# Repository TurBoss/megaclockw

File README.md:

# MegaClockW

Remote control your MD mods over wifi

MegaClockW Allows to control Region/Lang, video mode HZ, reset console and control the cpu mhz from 5.0 to 12.8

## Software Installation

Download Thonny or rshell

Upload the MicroPython uf2 on the Raspberry pi pico W
by booting in program mode by holding the push button and connect the USB cable

Upload the project files found in the src directory to the root of the pico using Thonny or rshell

https://github.com/dhylands/rshell

https://github.com/thonny/thonny/releases

https://micropython.org/download/rp2-pico-w/

## Hardware Installation

## Development

* [GitHub Repo](https://github.com/TurBoss/megaclockw/)
* [Issue Tracker](https://github.com/TurBoss/megaclockw/issues)

## Documentation and Help

* [Discord](https://discord.gg/8Ck5gNkA)

## DISCLAIMER

THE AUTHORS OF THIS SOFTWARE ACCEPT ABSOLUTELY NO LIABILITY FOR
ANY HARM OR LOSS RESULTING FROM ITS USE.  IT IS _EXTREMELY_ UNWISE
TO RELY ON SOFTWARE ALONE FOR SAFETY.  Any machinery capable of
harming persons must have provisions for completely removing power
from all motors, etc, before persons enter any danger area.  All
machinery must be designed to comply with local and national safety
codes, and the authors of this software can not, and do not, take
any responsibility for such compliance.

This software is released under the GPLv3.

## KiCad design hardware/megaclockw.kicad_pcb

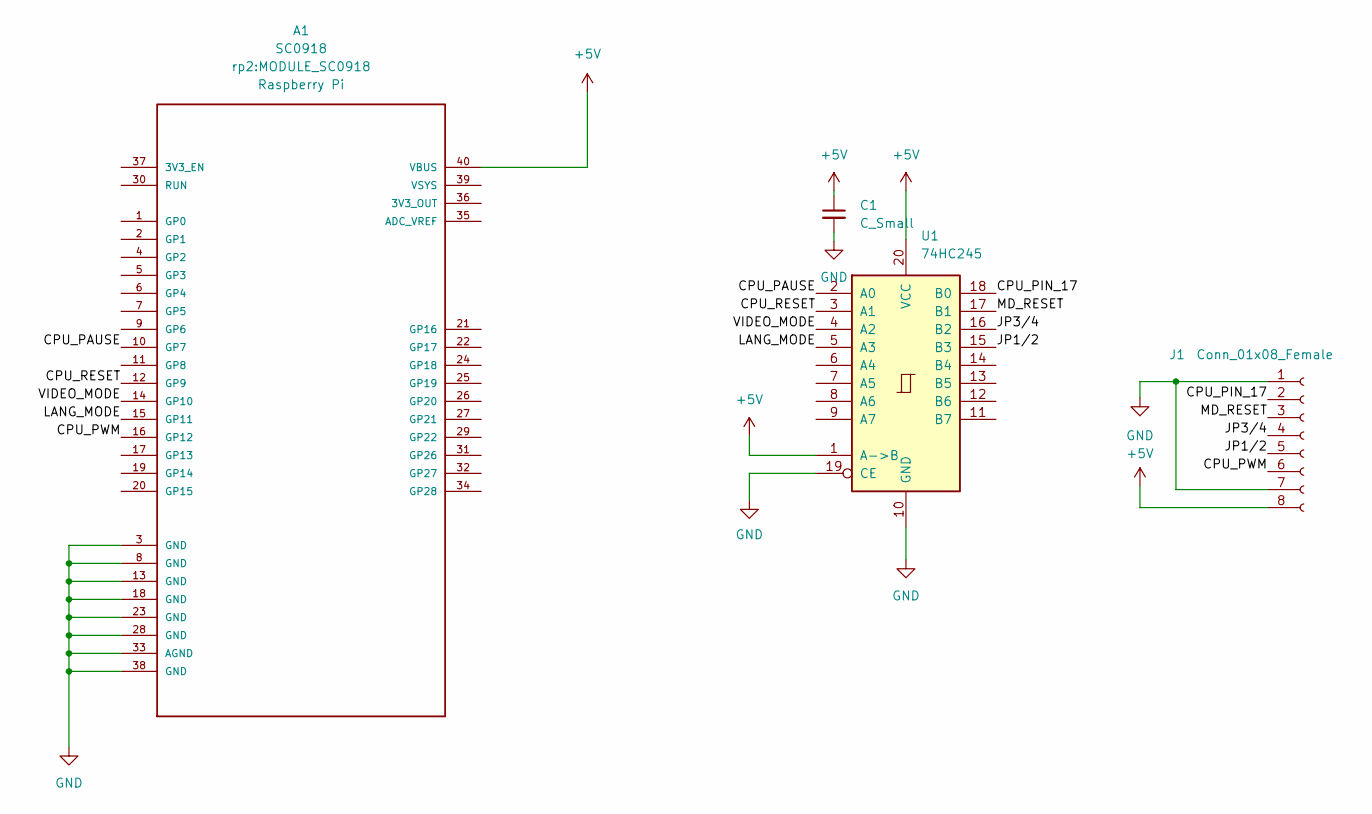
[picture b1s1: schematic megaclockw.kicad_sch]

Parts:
A1: SC0918; MODULE_SC0918; PARTREV 1.6
C1: C_Small; C_0603_1608Metric
J1: Conn_01x08_Female; PinSocket_1x08_P2.54mm_Vertical
U1: 74HC245; SOIC-20W_7.5x12.8mm_P1.27mm

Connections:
+5V: A1.40 (VBUS), C1.1, J1.8, U1.1 (A->B), U1.20 (VCC)
/CPU_PAUSE: A1.10 (GP7), U1.2 (A0)
/CPU_PIN_17: J1.2, U1.18 (B0)
/CPU_PWM: A1.16 (GP12), J1.6
/CPU_RESET: A1.12 (GP9), U1.3 (A1)
/JP1/2: J1.5, U1.15 (B3)
/JP3/4: J1.4, U1.16 (B2)
/LANG_MODE: A1.15 (GP11), U1.5 (A3)
/MD_RESET: J1.3, U1.17 (B1)
/VIDEO_MODE: A1.14 (GP10), U1.4 (A2)
GND: A1.3 (GND), A1.8 (GND), A1.13 (GND), A1.18 (GND), A1.23 (GND), A1.28 (GND), A1.33 (AGND), A1.38 (GND), C1.2, J1.1, J1.7, U1.10 (GND), U1.19 (CE)

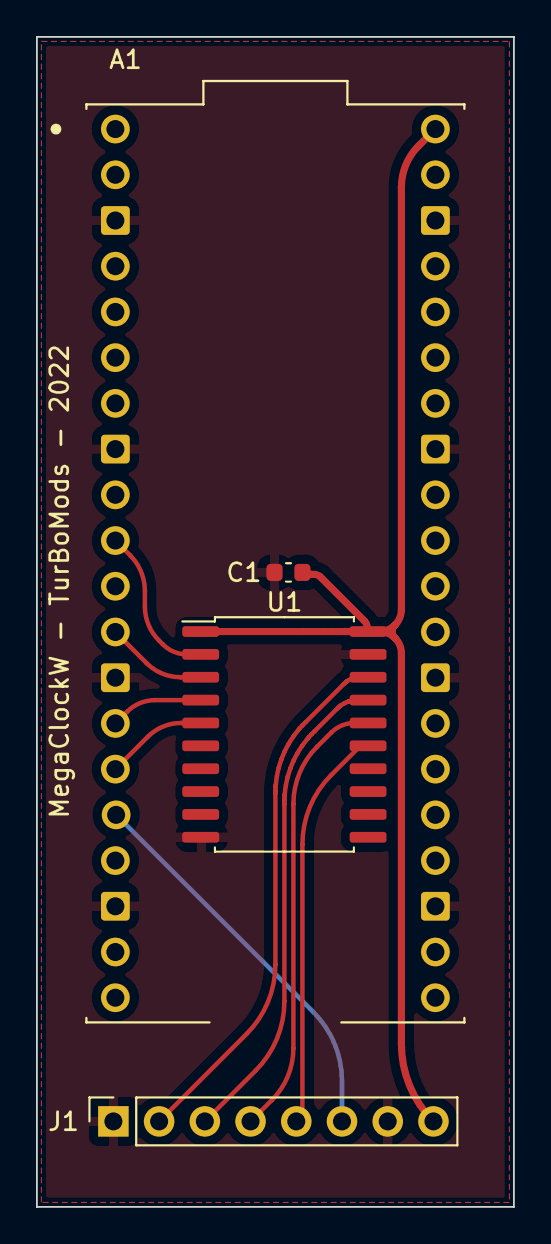
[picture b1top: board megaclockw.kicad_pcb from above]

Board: 2 copper layers, 26.5 x 65.0 mm, 4 parts (0 on the bottom side), 11 nets.

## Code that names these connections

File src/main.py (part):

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    lang_gpio = 11;
    pwm_gpio = 12;
    
cpu_pause_pin = Pin(pause_gpio, Pin.OUT)  # CPU pause
cpu_reset_pin = Pin(reset_gpio, Pin.OUT)  # console reset
video_pin = Pin(videp_gpio, Pin.OUT)  # video mode  JP3/4
lang_pin = Pin(lang_gpio, Pin.OUT)  # region JP1/2
    
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    led_pin = Pin(led_gpio, mode=Pin.OUT)
    led = Signal(led_pin, invert=False)

cpu_pause = Signal(cpu_pause_pin, invert=False)
cpu_reset = Signal(cpu_reset_pin, invert=False)
video = Signal(video_pin, invert=False)
lang = Signal(lang_pin, invert=False)

cpu_pwm = PWM(Pin(pwm_gpio))
cpu_pwm.duty_u16(32768) #  50% dutty cycle
# cpu_pwm.freq(1000000)

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
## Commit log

2022-12-22 main
2022-12-22 ignore eclipse project files
2022-12-22 add reference links
2022-12-22 fix readme and ignore more eclipse files
2022-12-22 Add GNU GPL v3 license
2022-12-23 move source to src dir add docs dir with schematics
2022-12-23 FIX readme
2022-12-23 add kicad files
2022-12-23 better power lines
2022-12-23 support esp32
2022-12-23 minor fixes esp32 and rp2
